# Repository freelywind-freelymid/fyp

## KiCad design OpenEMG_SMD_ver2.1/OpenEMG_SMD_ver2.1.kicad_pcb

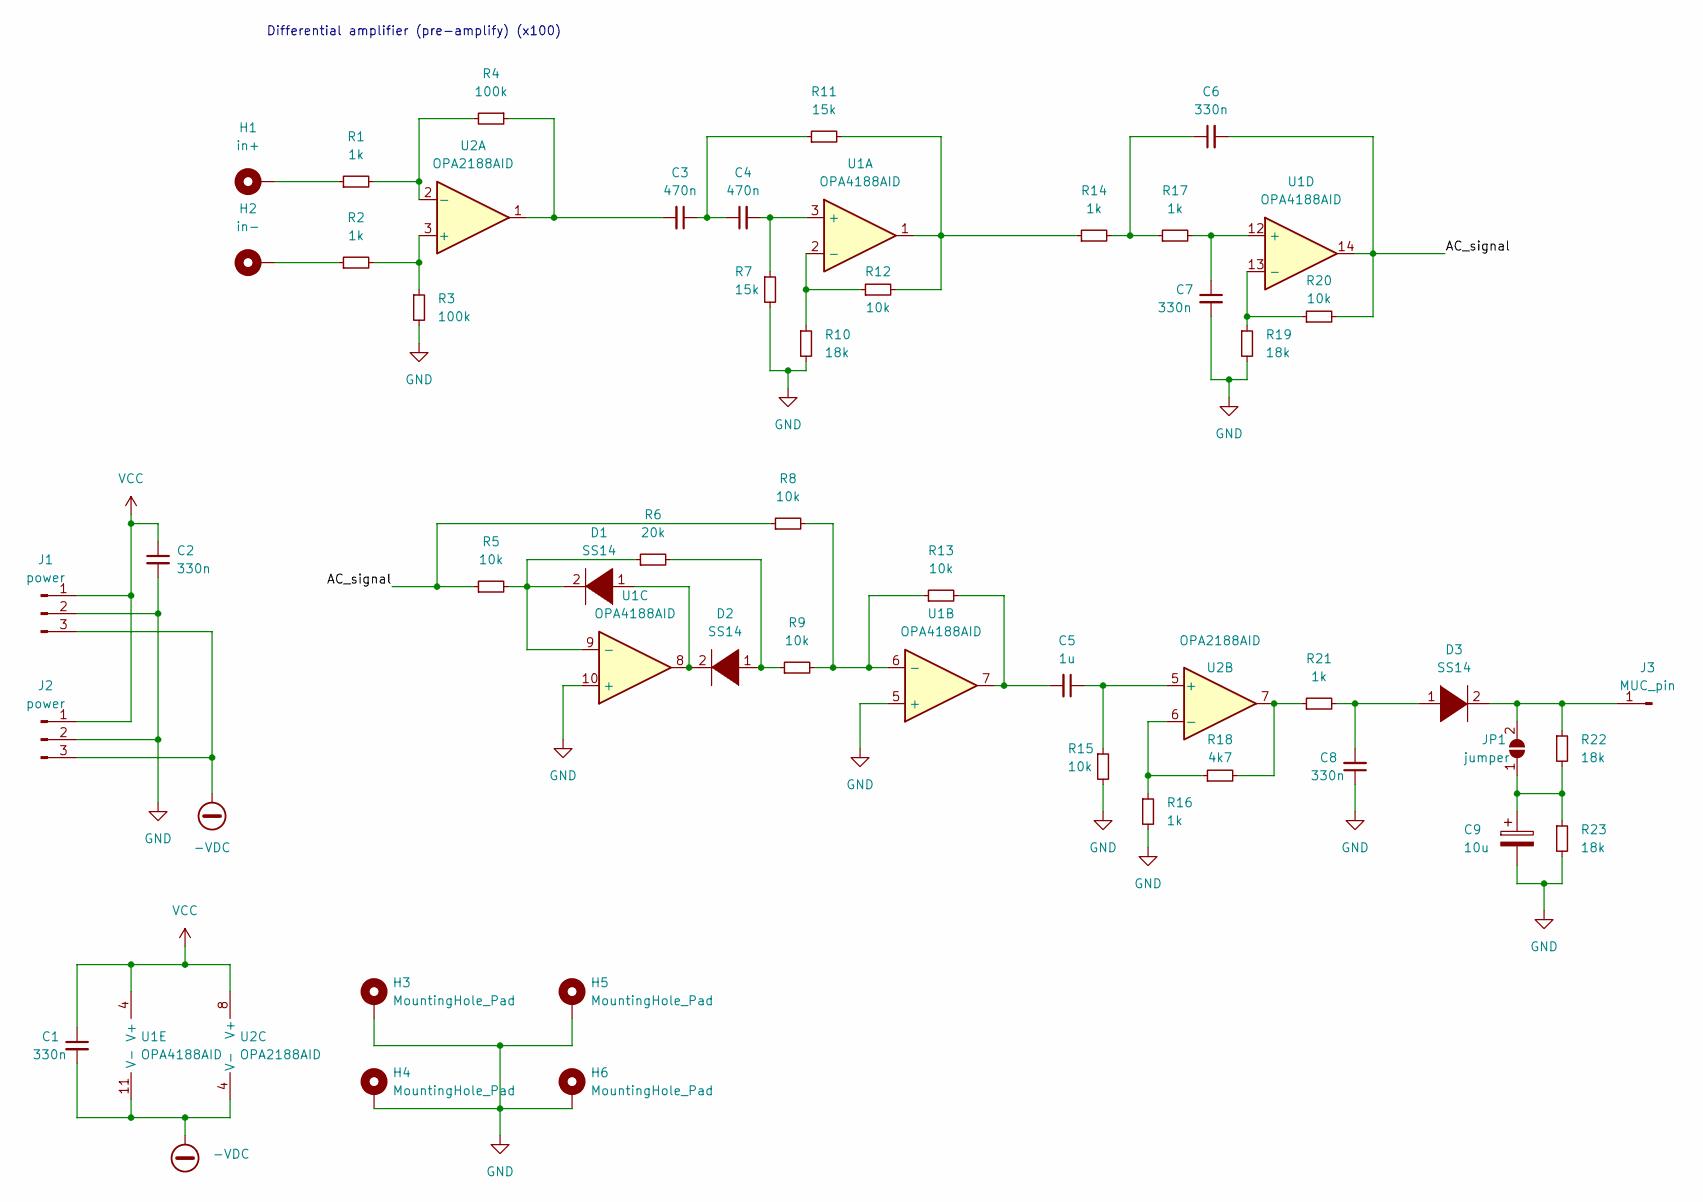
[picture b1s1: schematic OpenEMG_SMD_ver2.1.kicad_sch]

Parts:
C1, C2, C6, C7, C8: 330n; C_0805_2012Metric
C3, C4: 470n; C_0805_2012Metric
C5: 1u; C_0805_2012Metric
C9: 10u; CP_Elec_6.3x4.5
D1, D2, D3: SS14; D_SMA
H1: in+; MountingHole_6mm
H2: in-; MountingHole_6mm
H3, H4, H5, H6: MountingHole_Pad; MountingHole_2.2mm_M2_Pad_Via
J1, J2: power; PinHeader_1x03_P2.54mm_Vertical
J3: MUC_pin; PinHeader_1x01_P2.54mm_Vertical
JP1: jumper; SolderJumper-2_P1.3mm_Open_Pad1.0x1.5mm
R1, R2, R14, R16, R17, R21: 1k; R_0805_2012Metric
R3, R4: 100k; R_0805_2012Metric
R5, R8, R9, R12, R13, R15, R20: 10k; R_0805_2012Metric
R6: 20k; R_0805_2012Metric
R7, R11: 15k; R_0805_2012Metric
R10, R19, R22, R23: 18k; R_0805_2012Metric
R18: 4k7; R_0805_2012Metric
U1: OPA4188AID; SOIC-14_3.9x8.7mm_P1.27mm
U2: OPA2188AID; SOIC-8_3.9x4.9mm_P1.27mm

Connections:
-VDC: C1.2, J1.3, J2.3, U1.11 (V-), U2.4 (V-)
/AC_signal: C6.2, R5.1, R8.1, R20.2, U1.14
GND: C2.2, C7.2, C8.1, C9.2, H3.1, H4.1, H5.1, H6.1, J1.2, J2.2, R3.2, R7.2, R10.2, R15.2, R16.2, R19.2, R23.2, U1.5 (+), U1.10 (+)
unnamed: C3.1, C4.1, R11.1
unnamed: C3.2, R4.1, U2.1
unnamed: C4.2, R7.1, U1.3 (+)
unnamed: C5.1, R15.1, U2.5 (+)
unnamed: C5.2, R13.2, U1.7
unnamed: C6.1, R14.2, R17.1
unnamed: C7.1, R17.2, U1.12 (+)
unnamed: C8.2, D3.1 (K), R21.2
unnamed: C9.1, JP1.1 (A), R22.2, R23.1
unnamed: D1.1 (K), D2.2 (A), U1.8
unnamed: D1.2 (A), R5.2, R6.1, U1.9 (-)
unnamed: D2.1 (K), R6.2, R9.1
unnamed: D3.2 (A), J3.1, JP1.2 (B), R22.1
unnamed: H1.1, R1.1
unnamed: H2.1, R2.1
unnamed: R1.2, R4.2, U2.2 (-)
unnamed: R2.2, R3.1, U2.3 (+)
unnamed: R10.1, R12.1, U1.2 (-)
unnamed: R11.2, R12.2, R14.1, U1.1
unnamed: R8.2, R9.2, R13.1, U1.6 (-)
unnamed: R16.1, R18.1, U2.6 (-)
unnamed: R18.2, R21.1, U2.7
unnamed: R19.1, R20.1, U1.13 (-)
VCC: C1.1, C2.1, J1.1, J2.1, U1.4 (V+), U2.8 (V+)

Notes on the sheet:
Differential amplifier (pre-amplify) (x100)

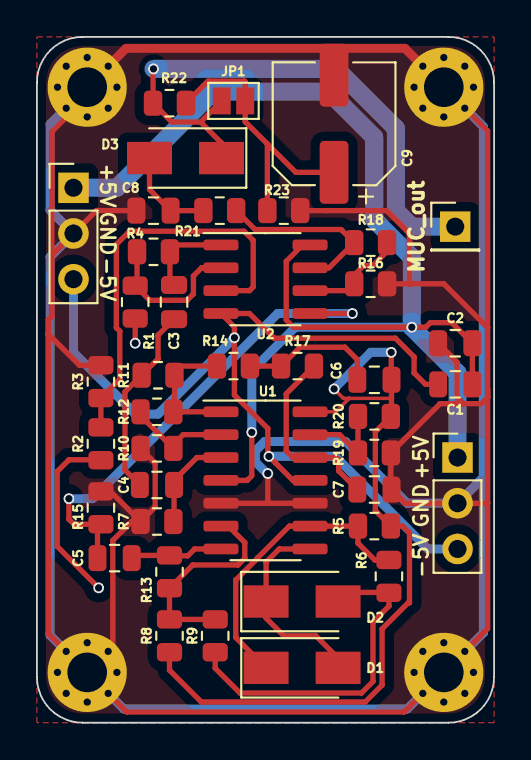
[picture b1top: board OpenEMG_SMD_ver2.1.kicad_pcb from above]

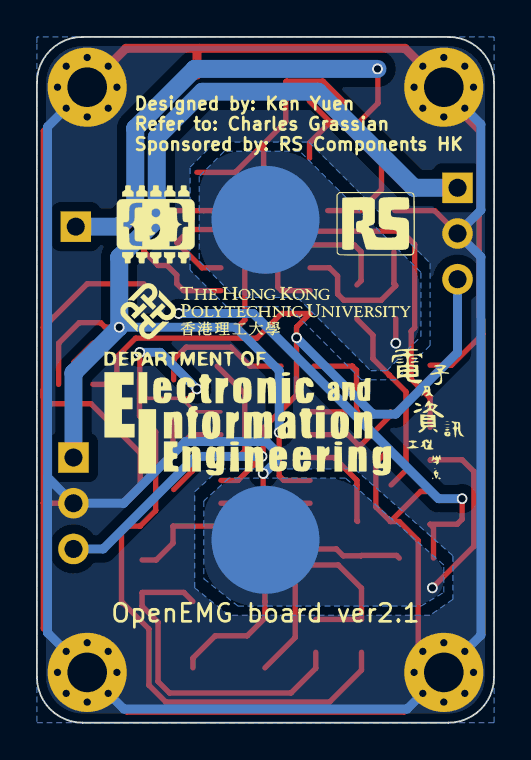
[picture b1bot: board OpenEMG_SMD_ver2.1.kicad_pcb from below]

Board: 2 copper layers, 25.4 x 38.1 mm, 51 parts (4 on the bottom side), 27 nets.

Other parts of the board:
G1: LOGO; rs_icon_1
G2: LOGO; eie_icon_1
G3: LOGO; polyu_icon_1
G4: LOGO; charles'_lab_icon

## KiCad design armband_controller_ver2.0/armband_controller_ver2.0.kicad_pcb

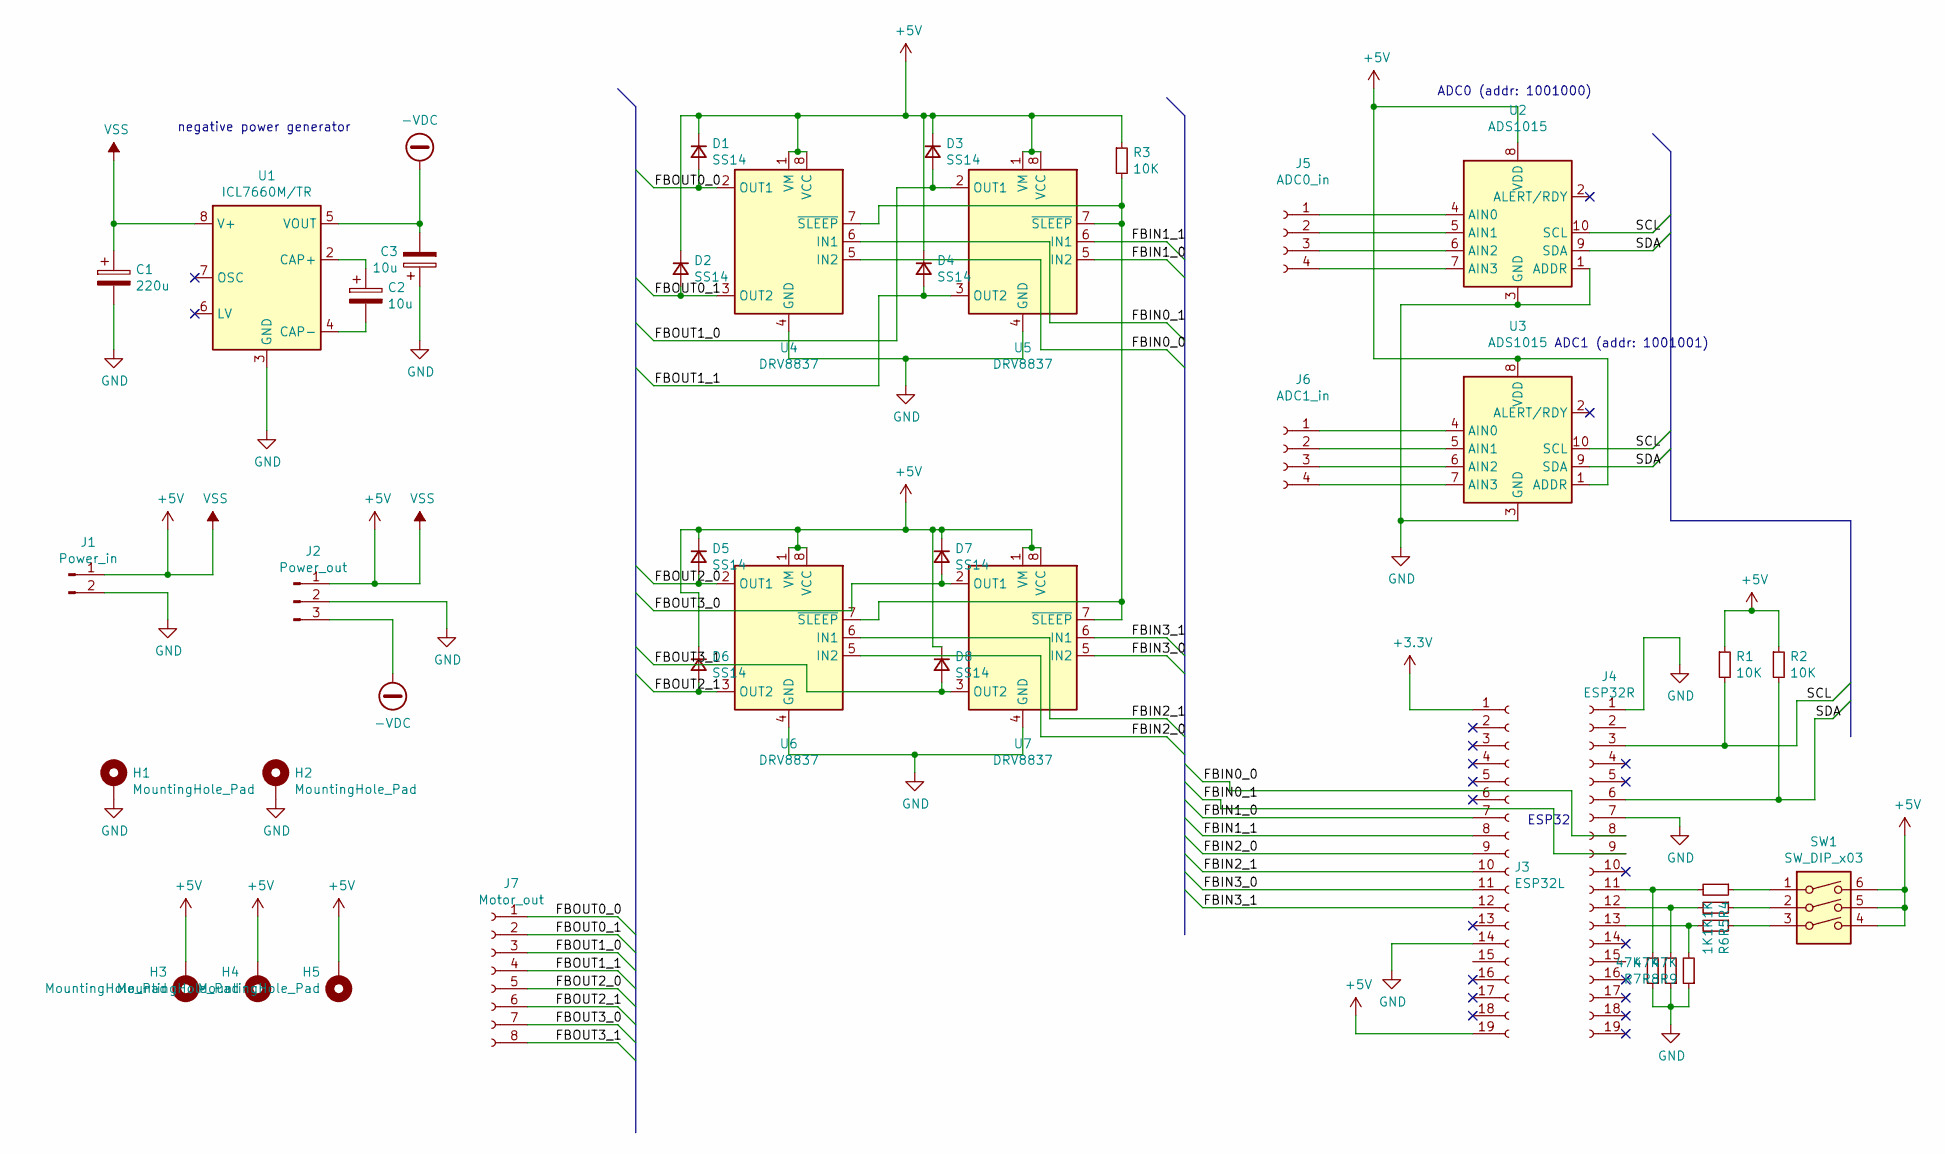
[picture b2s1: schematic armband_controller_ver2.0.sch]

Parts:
C1: 220u; CP_Elec_6.3x4.5
C2, C3: 10u; CP_Elec_6.3x4.5
D1, D2, D3, D4, D5, D6, D7, D8: SS14; D_SMA
H1, H2, H3, H4, H5: MountingHole_Pad; MountingHole_2.2mm_M2_Pad
J1: Power_in; PinHeader_1x02_P2.54mm_Vertical
J2: Power_out; PinHeader_1x03_P2.54mm_Vertical
J3: ESP32L; PinSocket_1x19_P2.54mm_Vertical
J4: ESP32R; PinSocket_1x19_P2.54mm_Vertical
J5: ADC0_in; PinSocket_1x04_P2.54mm_Vertical
J6: ADC1_in; PinSocket_1x04_P2.54mm_Vertical
J7: Motor_out; PinSocket_1x08_P2.54mm_Vertical
R1, R2, R3: 10K; R_0805_2012Metric
R4, R5, R6: 1K; R_0805_2012Metric
R7, R8, R9: 47K; R_0805_2012Metric
SW1: SW_DIP_x03; SW_DIP_SPSTx03_Slide_6.7x9.18mm_W7.62mm_P2.54mm_LowProfile
U1: ICL7660M/TR; SOP-8_3.76x4.96mm_P1.27mm
U2, U3: ADS1015; TSSOP-10_3x3mm_P0.5mm
U4, U5, U6, U7: DRV8837; WSON-8-1EP_2x2mm_P0.5mm_EP0.9x1.6mm

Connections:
+5V: C1.1, D1.1 (K), D2.1 (K), D3.1 (K), D4.1 (K), D5.1 (K), D6.1 (K), D7.1 (K), D8.1 (K), H3.1, H4.1, H5.1, J1.1, J2.1, J3.19, R1.1, R2.1, R3.1, SW1.4, SW1.5, SW1.6, U1.8 (V+), U2.8 (VDD), U3.1 (ADDR), U3.8 (VDD), U4.1 (VM), U4.8 (VCC), U5.1 (VM), U5.8 (VCC), U6.1 (VM), U6.8 (VCC), U7.1 (VM), U7.8 (VCC)
-VDC: C3.2, J2.3, U1.5 (VOUT)
/FBIN0_0: J4.8, U4.5 (IN2)
/FBIN0_1: J4.9, U4.6 (IN1)
/FBIN1_0: J3.7, U5.5 (IN2)
/FBIN1_1: J3.8, U5.6 (IN1)
/FBIN2_0: J3.9, U6.5 (IN2)
/FBIN2_1: J3.10, U6.6 (IN1)
/FBIN3_0: J3.11, U7.5 (IN2)
/FBIN3_1: J3.12, U7.6 (IN1)
/FBOUT0_0: D1.2 (A), J7.1, U4.2 (OUT1)
/FBOUT0_1: D2.2 (A), J7.2, U4.3 (OUT2)
/FBOUT1_0: D3.2 (A), J7.3, U5.2 (OUT1)
/FBOUT1_1: D4.2 (A), J7.4, U5.3 (OUT2)
/FBOUT2_0: D5.2 (A), J7.5, U6.2 (OUT1)
/FBOUT2_1: D6.2 (A), J7.6, U6.3 (OUT2)
/FBOUT3_0: D7.2 (A), J7.7, U7.2 (OUT1)
/FBOUT3_1: D8.2 (A), J7.8, U7.3 (OUT2)
/SCL: J4.3, R1.2, U2.10 (SCL), U3.10 (SCL)
/SDA: J4.6, R2.2, U2.9 (SDA), U3.9 (SDA)
GND: C1.2, C3.1, H1.1, H2.1, J1.2, J2.2, J3.14, J4.1, J4.7, R7.1, R8.1, R9.1, U1.3 (GND), U2.1 (ADDR), U2.3 (GND), U3.3 (GND), U4.4 (GND), U4.9 (GND), U5.4 (GND), U5.9 (GND), U6.4 (GND), U6.9 (GND), U7.4 (GND), U7.9 (GND)
unnamed: C2.1, U1.2 (CAP+)
unnamed: C2.2, U1.4 (CAP-)
unnamed: J4.11, R4.2, R7.2
unnamed: J4.12, R5.2, R8.2
unnamed: J4.13, R6.2, R9.2
unnamed: J5.1, U2.4 (AIN0)
unnamed: J5.2, U2.5 (AIN1)
unnamed: J5.3, U2.6 (AIN2)
unnamed: J5.4, U2.7 (AIN3)
unnamed: J6.1, U3.4 (AIN0)
unnamed: J6.2, U3.5 (AIN1)
unnamed: J6.3, U3.6 (AIN2)
unnamed: J6.4, U3.7 (AIN3)
unnamed: R3.2, U4.7 (~SLEEP), U5.7 (~SLEEP), U6.7 (~SLEEP), U7.7 (~SLEEP)
unnamed: R4.1, SW1.1
unnamed: R5.1, SW1.2
unnamed: R6.1, SW1.3

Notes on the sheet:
ADC0 (addr: 1001000)
ADC1 (addr: 1001001)
ESP32
negative power generator

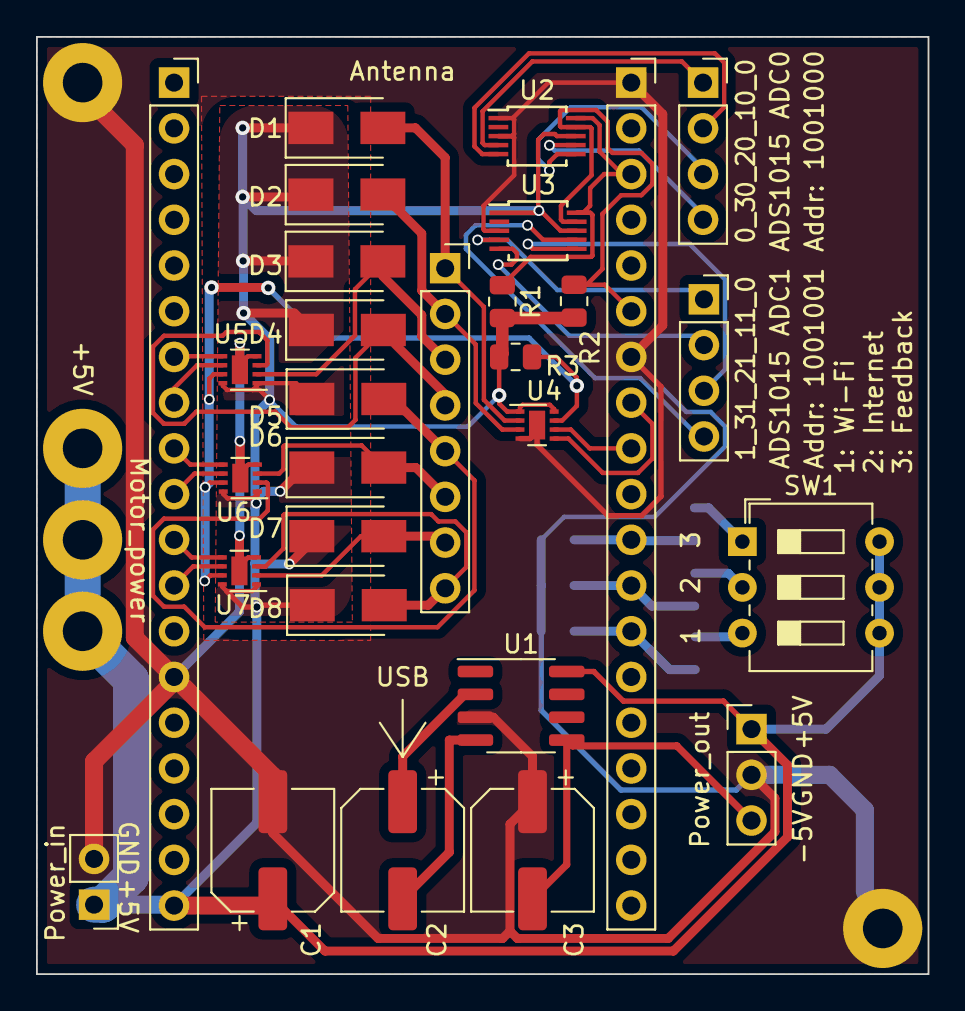
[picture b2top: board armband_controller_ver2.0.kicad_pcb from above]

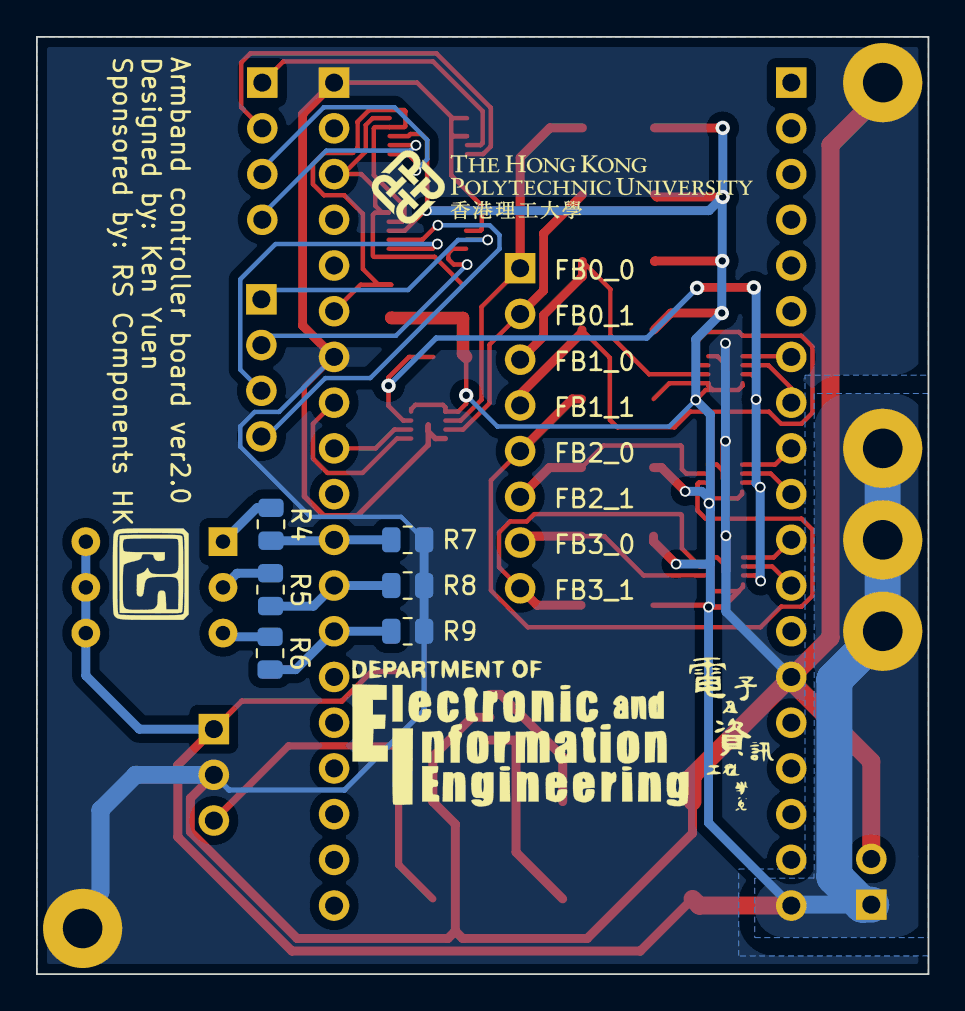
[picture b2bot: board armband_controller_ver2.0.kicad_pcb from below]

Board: 2 copper layers, 49.5 x 52.1 mm, 40 parts (6 on the bottom side), 38 nets.

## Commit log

2022-02-10 init.
2022-02-10 init
2022-02-11 updated the PCB
2022-03-28 頭痛, 吾打la~
2022-04-06 check point
